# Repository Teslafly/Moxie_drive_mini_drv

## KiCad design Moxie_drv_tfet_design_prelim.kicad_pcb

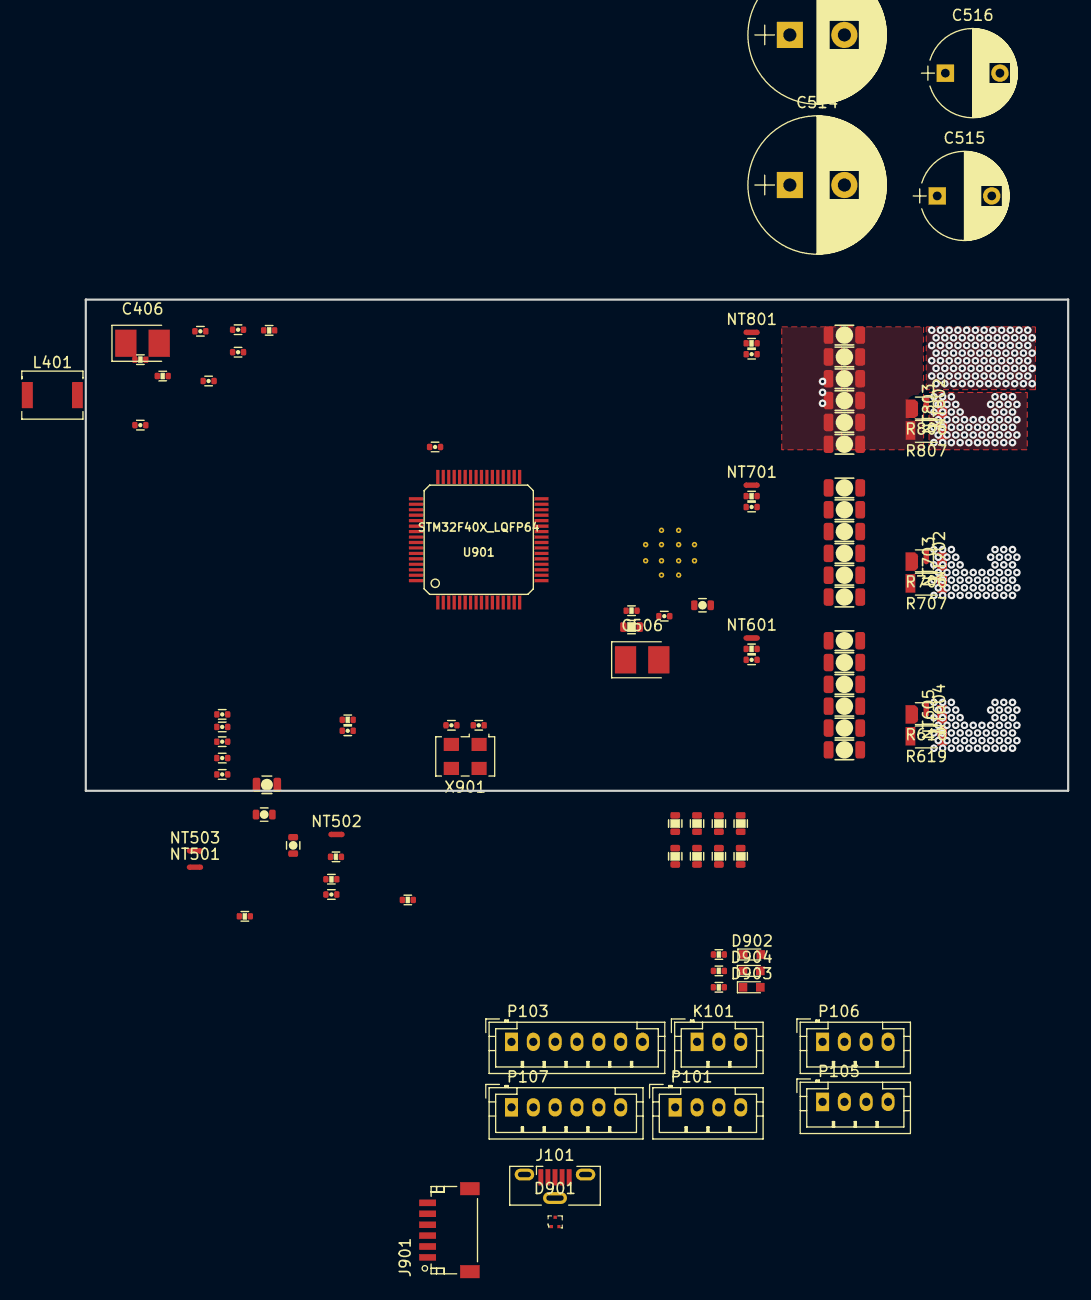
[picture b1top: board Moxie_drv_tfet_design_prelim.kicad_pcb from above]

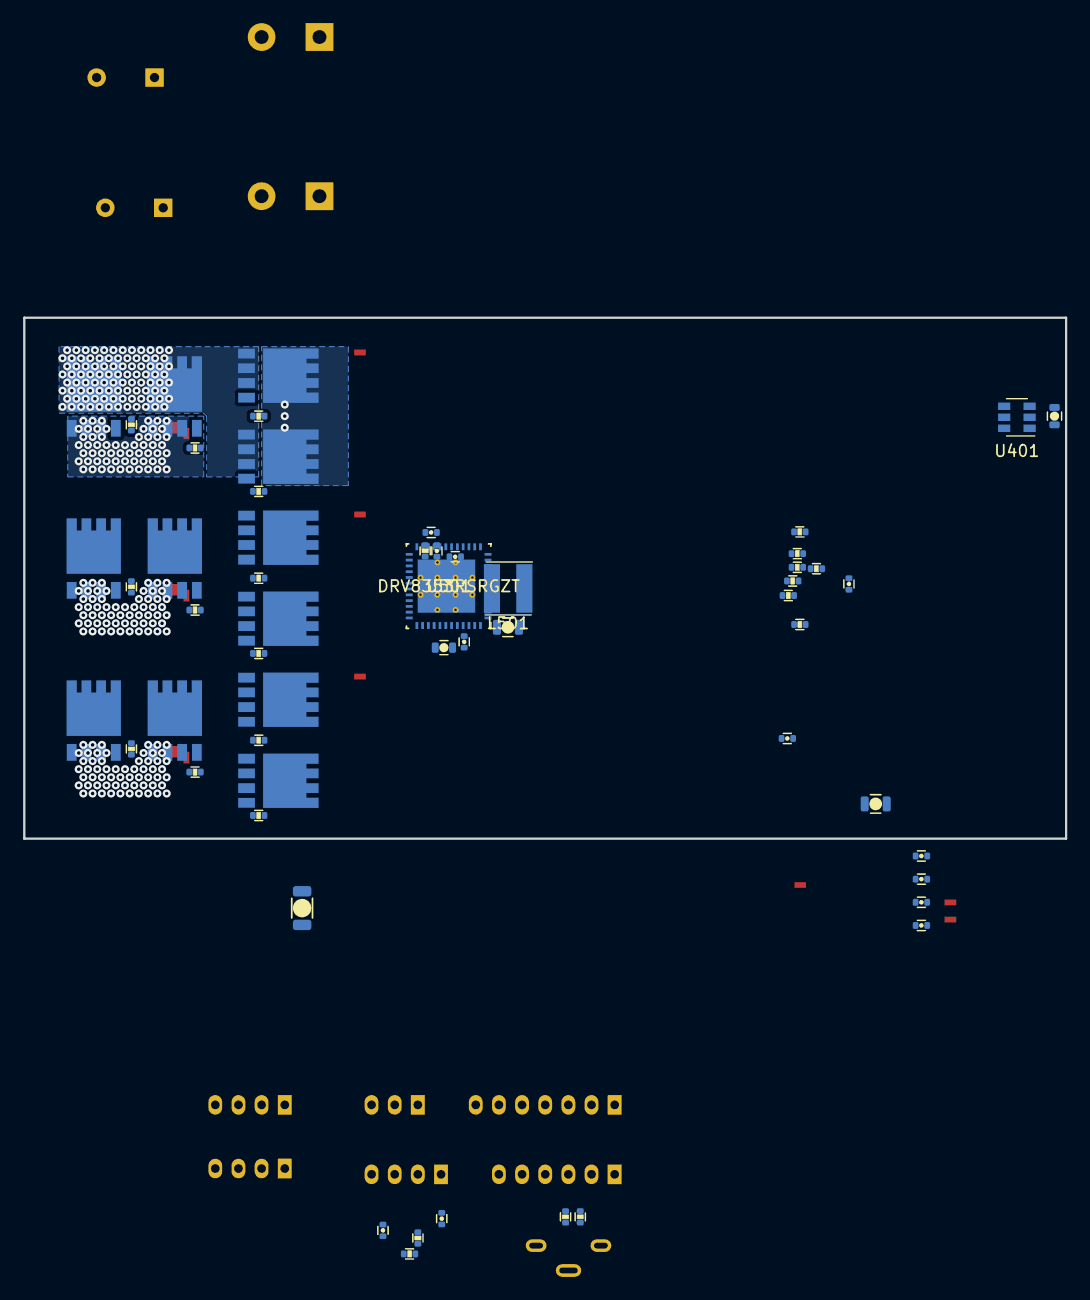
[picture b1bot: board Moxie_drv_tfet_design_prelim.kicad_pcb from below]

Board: 4 copper layers, 90.0 x 45.0 mm, 160 parts (56 on the bottom side), 109 nets, no tracks yet.

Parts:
C101, C107, C904: 100n; C_0402
C201: 4.7nf; C_0402
C202, C901, C902, C903, C905, C907, C909, C910, C911, C912: 2.2u; C_0402
C401: 2.2uf; C_0603
C402, C403, C404, C408: 100nf; C_0402
C405: 2.2uf; C_0402
C406: 100uf; CP_Tantalum_Case-B_EIA-3528-21_Reflow
C407: NP; C_0402
C501: 10uF; C_0805
C502: 1.5uF; C_1206
C503: 0.1uF; C_0603
C504: 0.1uF; C_0805
C505: 0.47uF; C_0402
C506: 0.1uF; CP_Tantalum_Case-B_EIA-3528-21_Reflow
C507: 0.047uF; C_0402
C508, C509, C511: 1uF; C_0603
C510: 0.01uF; C_0402
C512: 18nF; C_0402
C513: 22uF; C_0805
C514, C519: 560uF; CP_Radial_D12.5mm_P5.00mm
C515, C516: 20uF; CP_Radial_D8.0mm_P5.00mm
C601, C701, C801: 2.2nF; C_0402
C602, C603, C604, C605, C606, C607, C702, C703, C704, C705, C706, C707, C802, C803, C804, C805, C806, C807: 1uF; C_1206
C906, C908: 15p; C_0402
D901: TPD2EUSB30DRTR; SOT-3
D902: BLUE; LED_0603
D903: GREEN; LED_0603
D904: RED; LED_0603
J101: USB_B_Micro; USB_Micro-B_Vertical_Molex-105133-0001
J901: SWD; JST_SH_SM06B-SRSS-TB_06x1.00mm_Angled
K101: SERVO; JST_PH_B3B-PH-K_03x2.00mm_Straight
L401: 3.3uH; L_Neosid_Ms42
L501: 390uH; L_Bourns_SRN-4018
NT501, NT502, NT503, NT601, NT604, NT605, NT701, NT702, NT703, NT801, NT802, NT803: Net-Tie_2; NetTie-2_SMD_Pad0.5mm
P101: CANBUS; JST_PH_B4B-PH-K_04x2.00mm_Straight
P103: CTRL_SIGNALS; JST_PH_B7B-PH-K_07x2.00mm_Straight
P105: Serial1/tim4; JST_PH_B4B-PH-K_04x2.00mm_Straight
P106: I2C; JST_PH_B4B-PH-K_04x2.00mm_Straight
P107: HALL/Encoder; JST_PH_B6B-PH-K_06x2.00mm_Straight
Q601, Q602, Q603, Q604, Q701, Q702, Q703, Q704, Q801, Q802, Q803, Q804: TPH2R608NH,L1Q; SOP8_Advance
R101: 0Ω; R_0402
R102, R603, R703, R803: 100Ω; R_0402
R103, R104: 100kΩ; R_0402
R105, R106: 22R; R_0402
R107, R108, R109: 2k2Ω; R_0402
R110, R516: 10kΩ; R_0402
R201, R202: 120R; R_0402
R401, R901, R902, R903: 1k; R_0402
R402: R33.2k 0.1%; R_0402
R403: 10k 0.1%; R_0402
R501: 1kOhm; C_0402
R502: 10kΩ; C_0402
R503: 560kΩ; R_0402
R504: 200kΩ; R_0402
R505: 5.1kΩ; R_0402
R506: 1.0kΩ; R_0402
R507: 910mΩ; R_0603
R508, R510, R512, R514: 47kΩ; R_0603
R509, R511, R513, R515: 2.2kΩ; R_0603
R517: NTC 10kΩ; R_0402
R601, R602, R604, R605, R701, R702, R704, R705, R801, R802, R804, R805: 5Ω; R_0402
R618, R619, R706, R707, R806, R807: 1mΩ; R_1206
U401: TPS561201; SOT-23-6
U501: DRV8353RSRGZT; DRV8353RHRGZR
U901: STM32F40X_LQFP64; lqfp64_pad_mod
X901: 8MHz 10ppm; Oscillator_SMD_EuroQuartz_XO53-4pin_5.0x3.2mm

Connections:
+3V3: C202.1, C404.1, C405.1, C406.1, C407.1, C902.2, C905.2, C907.2, C909.2, C910.2, C911.2, C912.2, J901.1, L401.1, NT503.2, P103.1, P105.3, P106.3, P107.1, R101.2, R107.2, R108.2, R109.2, R110.2, R402.1, R501.1, R502.1, R516.1, R901.2, U901.1, U901.13, U901.19, U901.32, U901.48, U901.64
+12V: C401.1, C402.1, C501.1, C503.1, C513.1, R401.2, R507.2, U401.3, U501.5
+BATT: C502.1, C504.1, C511.1, C514.1, C515.1, C516.1, C519.1, C602.1, C603.1, C604.1, C605.1, C606.1, C607.1, C702.1, C703.1, C704.1, C705.1, C706.1, C707.1, C802.1, C803.1, C804.1, C805.1, C806.1, C807.1, Q601.1, Q603.1, Q701.1, Q703.1, Q801.1, Q803.1, R503.1, R514.1, U501.6, U501.43
/CAN_tranciever/CANH: P101.3, R201.1
/CAN_tranciever/CANL: P101.2, R202.1
/Microcontroller/ADC_BRAKE: P103.4, R104.1, U901.27
/Microcontroller/ADC_TEMP: C408.1, R516.2, R517.1, U901.24
/Microcontroller/ADC_THROTTLE: P103.3, R103.1, U901.26
/Microcontroller/ADC_VBUS: R514.2, R515.1, U901.11
/Microcontroller/BRAKE_SW: P103.6, U901.57
/Microcontroller/FAULT: R502.2, U501.28, U901.33
/Microcontroller/H1: U501.34, U901.41
/Microcontroller/H2: U501.36, U901.42
/Microcontroller/H3: U501.38, U901.43
/Microcontroller/HALL_1: P107.3, R107.1, U901.37
/Microcontroller/HALL_2: P107.4, R108.1, U901.38
/Microcontroller/HALL_3: P107.5, R109.1, U901.39
/Microcontroller/L1: U501.35, U901.34
/Microcontroller/L2: U501.37, U901.35
/Microcontroller/L3: U501.39, U901.36
/Microcontroller/LED_GREEN: R902.2, U901.3
/Microcontroller/LED_RED: R903.2, U901.4
/Microcontroller/SCL_2: P106.1, U901.29
/Microcontroller/SDA_2: P106.2, U901.30
/Microcontroller/SERVO: C101.2, R102.1, U901.17
/Microcontroller/TEMP_MOTOR: C107.2, P107.2, R110.1, U901.25
/Microcontroller/USART1_RX: P105.1, U901.59
/Microcontroller/USART1_TX: P105.2, U901.58
/Microcontroller/USB_DM: D901.2, R106.1, U901.44
/Microcontroller/USB_DP: D901.1, R105.1, U901.45
/Microcontroller/VCAP1: C903.2, U901.31
/Microcontroller/VCAP2: C901.2, U901.47
/drv_power_stage/3.3_IREF: C506.1, NT503.1, U501.26
/drv_power_stage/A_ISENSE: U501.25, U901.8
/drv_power_stage/A_VSENSE: R508.2, R509.1, U901.14
/drv_power_stage/B_ISENSE: U501.24, U901.9
/drv_power_stage/B_VSENSE: R510.2, R511.1, U901.15
/drv_power_stage/C_ISENSE: U501.23, U901.10
/drv_power_stage/C_VSENSE: R512.2, R513.1, U901.16
/drv_power_stage/DRV_SDO: R501.2, U501.29
/drv_power_stage/ENABLE: U501.33, U901.40
/drv_power_stage/GDRV_VSENSE: C512.1, R505.2, R506.1, U501.48
/drv_power_stage/PHASE_A: NT801.2, Q801.3, Q802.1, Q803.3, Q804.1, R508.1
/drv_power_stage/PHASE_B: NT601.2, Q601.3, Q602.1, Q603.3, Q604.1, R510.1
/drv_power_stage/PHASE_C: NT701.2, Q701.3, Q702.1, Q703.3, Q704.1, R512.1
/drv_power_stage/buck_rcl: R504.2, U501.46
/drv_power_stage/power_phase_A/H_GATE: R801.2, R804.2, U501.8
/drv_power_stage/power_phase_A/H_SWITCH: NT801.1, U501.9
/drv_power_stage/power_phase_A/L_GATE: R802.2, R805.2, U501.10
/drv_power_stage/power_phase_A/NR_SENSE: C801.1, R803.1, U501.12
/drv_power_stage/power_phase_A/PH_GND_LOW: NT802.2, Q802.3, Q804.3, R806.1, R807.1
/drv_power_stage/power_phase_A/PR_SENSE: C801.2, NT802.1, U501.11
/drv_power_stage/power_phase_B/H_GATE: R601.2, R604.2, U501.17
/drv_power_stage/power_phase_B/H_SWITCH: NT601.1, U501.16
/drv_power_stage/power_phase_B/L_GATE: R602.2, R605.2, U501.15
/drv_power_stage/power_phase_B/NR_SENSE: C601.1, R603.1, U501.13
/drv_power_stage/power_phase_B/PH_GND_LOW: NT604.2, Q602.3, Q604.3, R618.1, R619.1
/drv_power_stage/power_phase_B/PR_SENSE: C601.2, NT604.1, U501.14
/drv_power_stage/power_phase_C/H_GATE: R701.2, R704.2, U501.18
/drv_power_stage/power_phase_C/H_SWITCH: NT701.1, U501.19
/drv_power_stage/power_phase_C/L_GATE: R702.2, R705.2, U501.20
/drv_power_stage/power_phase_C/NR_SENSE: C701.1, R703.1, U501.22
/drv_power_stage/power_phase_C/PH_GND_LOW: NT702.2, Q702.3, Q704.3, R706.1, R707.1
/drv_power_stage/power_phase_C/PR_SENSE: C701.2, NT702.1, U501.21
GND: C101.1, C107.1, C201.2, C202.2, C401.2, C402.2, C404.2, C405.2, C406.2, C514.2, C515.2, C516.2, C519.2, C901.1, C903.1, C904.1, C906.2, C907.1, C908.2, C909.1, C910.1, C911.1, C912.1, D901.3, D902.2, D903.2, D904.2, J101.5, J101.6, J901.3, K101.3, NT501.2, NT502.2, P101.1, P103.2, P103.7, P105.4, P106.4, P107.6, R103.2, R104.2, R403.2, U401.1, U501.41, U901.18, U901.60, U901.63, X901.3
GNDA: C408.2, C506.2, C902.1, C905.1, NT501.1, U501.27, U901.12
GNDD: C501.2, C502.2, C503.2, C504.2, C505.2, C508.1, C509.2, C513.2, C602.2, C603.2, C604.2, C605.2, C606.2, C607.2, C702.2, C703.2, C704.2, C705.2, C706.2, C707.2, C802.2, C803.2, C804.2, C805.2, C806.2, C807.2, NT502.1, NT605.2, NT703.2, NT803.2, R504.1, R506.2, R509.2, R511.2, R513.2, R515.2, R517.2, R618.2, R619.2, R706.2, R707.2, R806.2, R807.2, U501.1, U501.49
NRST: C904.2, J901.5, U901.7
unnamed: C201.1, R201.2, R202.2
unnamed: C403.1, L401.2, U401.2
unnamed: C403.2, U401.6
unnamed: C407.2, R402.2, R403.1, U401.4
unnamed: C505.1, U501.44
unnamed: C507.1, U501.4
unnamed: C507.2, U501.3
unnamed: C508.2, U501.2
unnamed: C509.1, U501.40
unnamed: C510.1, U501.45
unnamed: C510.2, L501.2, U501.42
unnamed: C511.2, U501.7
unnamed: C512.2, L501.1, R505.1, R507.1
unnamed: C906.1, U901.5, X901.1
unnamed: C908.1, U901.6, X901.2
unnamed: D902.1, R901.1
unnamed: D903.1, R902.1
unnamed: D904.1, R903.1
unnamed: J101.2, R106.2
unnamed: J101.3, R105.2
unnamed: K101.1, R102.2
unnamed: K101.2, R101.1
unnamed: NT605.1, R603.2
unnamed: NT703.1, R703.2
unnamed: NT803.1, R803.2
unnamed: Q601.2, R601.1
unnamed: Q602.2, R602.1
unnamed: Q603.2, R604.1
unnamed: Q604.2, R605.1
unnamed: Q701.2, R701.1
unnamed: Q702.2, R702.1
unnamed: Q703.2, R704.1
unnamed: Q704.2, R705.1
unnamed: Q801.2, R801.1
unnamed: Q802.2, R802.1
unnamed: Q803.2, R804.1
unnamed: Q804.2, R805.1
unnamed: R401.1, U401.5
unnamed: R503.2, U501.47
SWCLK: J901.2, U901.49
SWDIO: J901.4, U901.46

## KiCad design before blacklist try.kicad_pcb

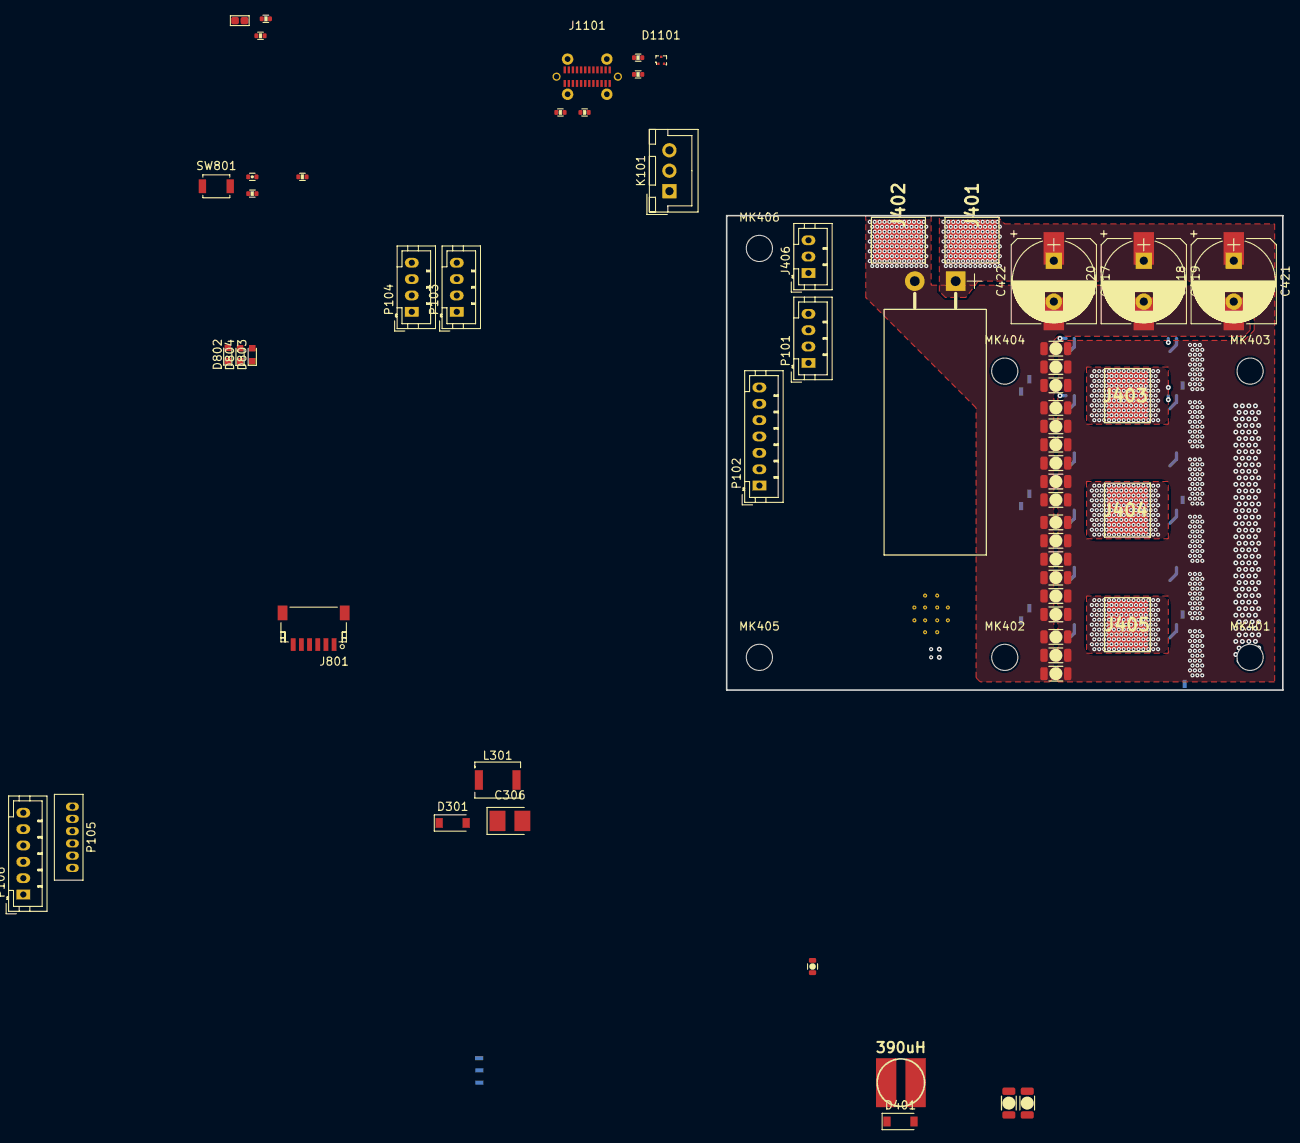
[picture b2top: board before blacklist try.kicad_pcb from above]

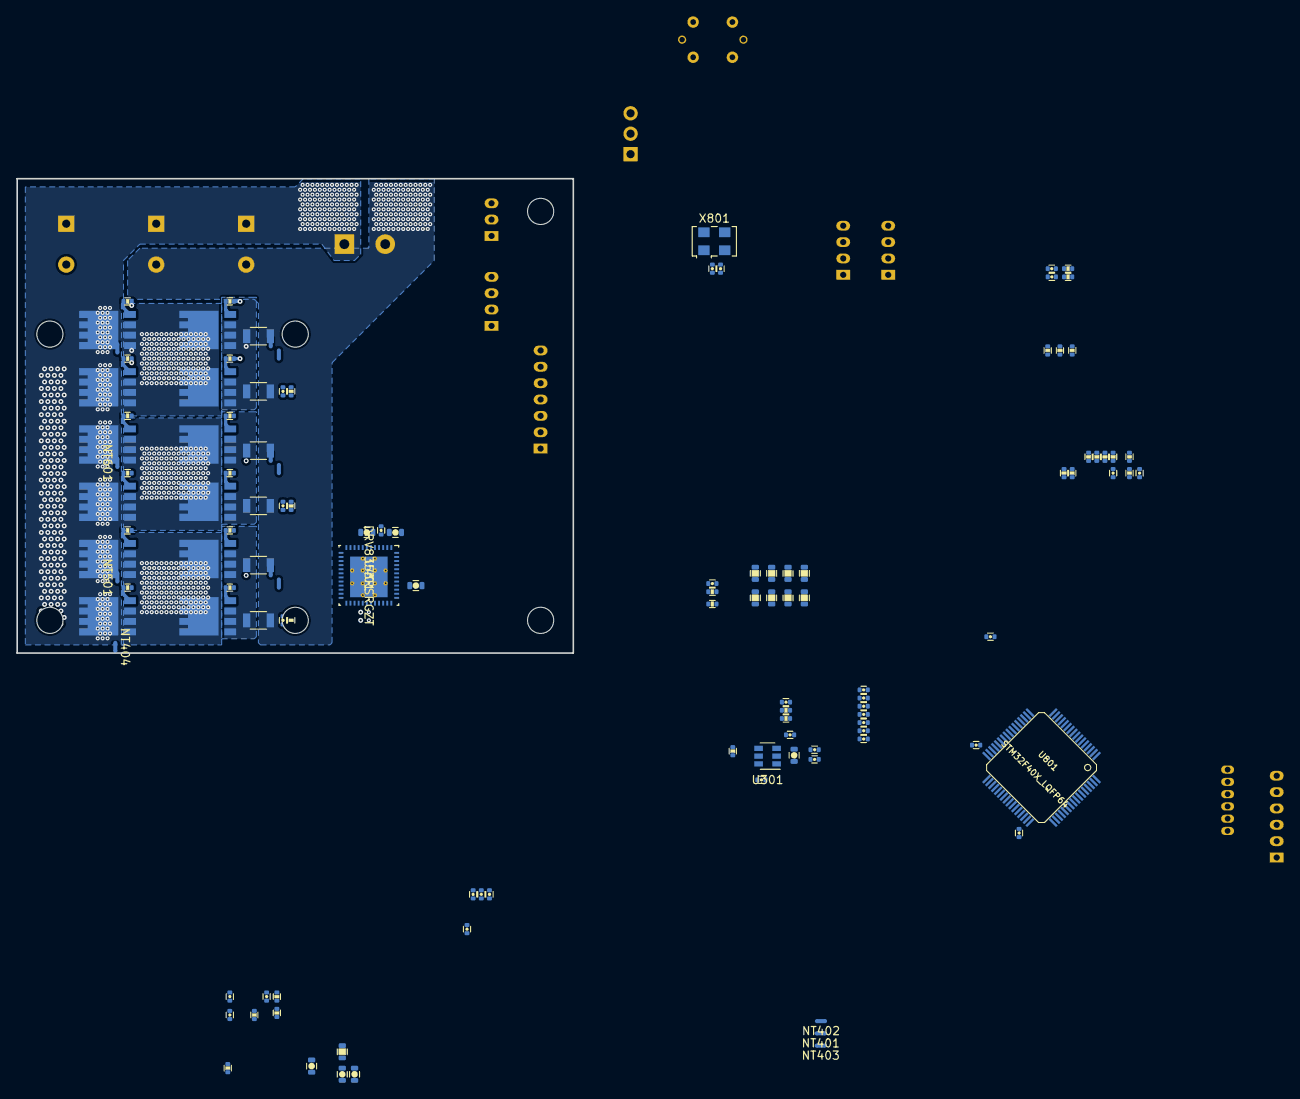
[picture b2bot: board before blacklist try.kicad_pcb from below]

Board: 4 copper layers, 68.0 x 58.0 mm, 190 parts (121 on the bottom side), 118 nets.

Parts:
C101, C102, C804, C813: 100n; C_0402
C201: 4.7nf; C_0402
C202, C801, C802, C803, C805, C807, C809, C810, C811, C812: 2.2u; C_0402
C301: 10uf; C_0603
C302, C303, C304, C423: 100nf; C_0402
C305: 2.2uf; C_0402
C306: 100uf; CP_Tantalum_Case-B_EIA-3528-21_Reflow
C307: NP; C_0402
C401, C402, C413: 10uF; C_0603
C403, C406: 0.1uF; C_0402
C404: 0.1uF; C_0603
C405: 0.47uF; C_0402
C407: 0.047uF; C_0402
C408, C409, C411: 1uF; C_0603
C410: 0.01uF; C_0402
C412: 18nF; C_0402
C414: 560uF; CP_Radial_D12.5mm_P5.00mm_horiz
C417, C419, C421: 56uF; CP_Radial_D10.0mm_P5.00mm
C418, C420, C422: 20uF; CP_Elec_10x10.5
C424, C425, C502, C503, C504, C505, C506, C507, C602, C603, C604, C605, C606, C607, C702, C703, C704, C705, C706, C707: 1uF; C_1206
C501, C601, C701: 2.2nF; C_0402
C806, C808: 15p; C_0402
D301: 1.5KExxA; D_SOD-123
D401: DFLS1100-7; D_SOD-123
D802: BLUE; LED_0603
D803: GREEN; LED_0603
D804: RED; LED_0603
D1101: TPD2EUSB30DRTR; SOT-3
J401: +Vbat; 1PAD_6x5mm
J402: Gnd; 1PAD_6x5mm
J403: A; 1PAD_6x5mm
J404: B; 1PAD_6x5mm
J405: C; 1PAD_6x5mm
J406: Conn_01x03; JST_PH_B3B-PH-K_03x2.00mm_Straight
J801: SWD; JST_SH_SM06B-SRSS-TB_06x1.00mm_Angled
J1101: USB_C_Receptacle; USB_C_receptacle_vertical
JP401: pwr_ctl_byp; J_0603
K101: SERVO; JST_XH_B03B-XH-A_03x2.50mm_Straight
L301: 3.3uH; L_Neosid_Ms42
L401: 390uH; inductor_smd_5.8mmx4.8hmm
MK401, MK402, MK403, MK404, MK405, MK406: Mounting_Hole; MountingHole_3.2mm_M3_DIN965
NT401, NT402, NT403, NT404, NT501, NT502, NT503, NT601, NT602, NT603, NT701, NT702, NT703: Net-Tie_2; NetTie-2_SMD_Pad0.5mm
P101: CANBUS; JST_PH_B4B-PH-K_04x2.00mm_Straight
P102: CTRL_SIGNALS; JST_PH_B7B-PH-K_07x2.00mm_Straight
P103: Serial1/tim4; JST_PH_B4B-PH-K_04x2.00mm_Straight
P104: I2C; JST_PH_B4B-PH-K_04x2.00mm_Straight
P105: HALL/Encoder; simple_jst-zh_1.5mm_unfinished
P106: HALL/Encoder; JST_PH_B6B-PH-K_06x2.00mm_Straight
Q501, Q502, Q503, Q504, Q601, Q602, Q603, Q604, Q701, Q702, Q703, Q704: TPH2R608NH,L1Q; SOP8_Advance
R101: 0Ω; R_0402
R102, R501, R601, R701: 100Ω; R_0402
R103, R104: 100kΩ; R_0402
R107, R108, R109: 2k2Ω; R_0402
R110, R416: 10kΩ; R_0402
R201, R202: 120R; R_0402
R301, R801, R802, R803: 1k; R_0402
R302: R33.2k 0.1%; R_0402
R303: 10k 0.1%; R_0402
R401: 1kOhm; C_0402
R402: 10kΩ; C_0402
R403: 560kΩ; R_0402
R404: 200kΩ; R_0402
R405: 5.1kΩ; R_0402
R406: 1.0kΩ; R_0402
R407: 910mΩ; R_0603
R408, R410, R412, R414: 47kΩ; R_0603
R409, R411, R413, R415: 2.2kΩ; R_0603
R417: NTC 10kΩ; R_0402
R418, R804: 10k; R_0402
R419: 22k?; R_0402
R420: 100; R_0402
R502, R503, R504, R505, R602, R603, R604, R605, R702, R703, R704, R705: 5Ω; R_0402
R506, R507, R606, R607, R706, R707: 1mΩ; R_1206
R1101, R1102: 22R; R_0402
R1103, R1104: 5.1k; R_0402
SW801: SW_Push; SW_SPST_B3U-1000P
U301: TPS561201; SOT-23-6
U401: DRV8353RSRGZT; DRV8353RHRGZR
U801: STM32F40X_LQFP64; lqfp64_pad_mod
X801: 8MHz 10ppm; Oscillator_SMD_EuroQuartz_XO53-4pin_5.0x3.2mm

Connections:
+3V3: C202.1, C304.1, C305.1, C306.1, C307.1, C802.2, C805.2, C807.2, C809.2, C810.2, C811.2, C812.2, D301.1, J801.1, L301.1, NT403.2, P102.1, P103.3, P104.3, P105.6, R101.2, R107.2, R108.2, R109.2, R110.2, R302.1, R401.1, R402.1, R416.1, R801.2, SW801.2, U801.1, U801.13, U801.19, U801.32, U801.48, U801.64
+15V: C301.1, C302.1, C401.1, C402.1, C403.1, C413.1, R301.2, R407.2, R420.2, U301.3, U401.5
+BATT: C414.1, C417.1, C418.1, C419.1, C420.1, C421.1, C422.1, C502.1, C503.1, C504.1, C505.1, C506.1, C507.1, C602.1, C603.1, C604.1, C605.1, C606.1, C607.1, C702.1, C703.1, C704.1, C705.1, C706.1, C707.1, J401.1, JP401.1, NT404.1, Q501.1, Q503.1, Q601.1, Q603.1, Q701.1, Q703.1, R414.1, R418.1
/CAN_tranciever/CANH: P101.3, R201.1
/CAN_tranciever/CANL: P101.2, R202.1
/Microcontroller/ADC_BRAKE: P102.4, R104.1, U801.27
/Microcontroller/ADC_TEMP: C423.1, R416.2, R417.1, U801.24
/Microcontroller/ADC_THROTTLE: P102.3, R103.1, U801.26
/Microcontroller/ADC_VBUS: R414.2, R415.1, U801.11
/Microcontroller/BOOT_0: C813.2, R804.1, SW801.1, U801.60
/Microcontroller/BRAKE_SW: P102.6, U801.57
/Microcontroller/FAULT: R402.2, U401.28, U801.33
/Microcontroller/H1: U401.34, U801.41
/Microcontroller/H2: U401.36, U801.42
/Microcontroller/H3: U401.38, U801.43
/Microcontroller/HALL_1: P105.4, R107.1, U801.37
/Microcontroller/HALL_2: P105.3, R108.1, U801.38
/Microcontroller/HALL_3: P105.2, R109.1, U801.39
/Microcontroller/L1: U401.35, U801.34
/Microcontroller/L2: U401.37, U801.35
/Microcontroller/L3: U401.39, U801.36
/Microcontroller/LED_GREEN: R802.2, U801.3
/Microcontroller/LED_RED: R803.2, U801.4
/Microcontroller/SCL_2: P104.1, U801.29
/Microcontroller/SDA_2: P104.2, U801.30
/Microcontroller/SERVO: C101.2, R102.1, U801.17
/Microcontroller/TEMP_MOTOR: C102.2, P105.5, R110.1, U801.25
/Microcontroller/USART1_RX: P103.1, U801.59
/Microcontroller/USART1_TX: P103.2, U801.58
/Microcontroller/VCAP1: C803.2, U801.31
/Microcontroller/VCAP2: C801.2, U801.47
/USB-C connector/D+: D1101.1, R1102.1, U801.45
/USB-C connector/D-: D1101.2, R1101.1, U801.44
/drv_power_stage/3.3_IREF: C406.1, NT403.1, U401.26
/drv_power_stage/A_ISENSE: U401.25, U801.8
/drv_power_stage/A_VSENSE: R408.2, R409.1, U801.14
/drv_power_stage/BK_BST_C: C410.1, U401.45
/drv_power_stage/BK_RT_SD: R403.2, U401.47
/drv_power_stage/BK_SW: C410.2, D401.1, L401.2, U401.42
/drv_power_stage/BK_VCC: C405.1, U401.44
/drv_power_stage/BK_VIN: C404.1, C424.1, C425.1, JP401.2, R403.1, U401.43
/drv_power_stage/BK_VOUT_RIPP: C412.2, L401.1, R405.1, R407.1
/drv_power_stage/B_ISENSE: U401.24, U801.9
/drv_power_stage/B_VSENSE: R410.2, R411.1, U801.15
/drv_power_stage/C_ISENSE: U401.23, U801.10
/drv_power_stage/C_VSENSE: R412.2, R413.1, U801.16
/drv_power_stage/DRV_SDO: R401.2, U401.29
/drv_power_stage/ENABLE: U401.33, U801.40
/drv_power_stage/GDRV_VSENSE: C412.1, R405.2, R406.1, U401.48
/drv_power_stage/PHASE_A: J403.1, NT701.2, Q701.3, Q702.1, Q703.3, Q704.1, R408.1
/drv_power_stage/PHASE_B: J404.1, NT601.2, Q601.3, Q602.1, Q603.3, Q604.1, R410.1
/drv_power_stage/PHASE_C: J405.1, NT501.2, Q501.3, Q502.1, Q503.3, Q504.1, R412.1
/drv_power_stage/buck_rcl: R404.2, U401.46
/drv_power_stage/dvdd: C409.1, U401.40
/drv_power_stage/power_phase_A/H_GATE: R702.2, R704.2, U401.8
/drv_power_stage/power_phase_A/H_SWITCH: NT701.1, U401.9
/drv_power_stage/power_phase_A/L_GATE: R703.2, R705.2, U401.10
/drv_power_stage/power_phase_A/NR_SENSE: C701.1, R701.1, U401.12
/drv_power_stage/power_phase_A/PH_GND_LOW: NT702.2, Q702.3, Q704.3, R706.1, R707.1
/drv_power_stage/power_phase_A/PR_SENSE: C701.2, NT702.1, U401.11
/drv_power_stage/power_phase_B/H_GATE: R602.2, R604.2, U401.17
/drv_power_stage/power_phase_B/H_SWITCH: NT601.1, U401.16
/drv_power_stage/power_phase_B/L_GATE: R603.2, R605.2, U401.15
/drv_power_stage/power_phase_B/NR_SENSE: C601.1, R601.1, U401.13
/drv_power_stage/power_phase_B/PH_GND_LOW: NT602.2, Q602.3, Q604.3, R606.1, R607.1
/drv_power_stage/power_phase_B/PR_SENSE: C601.2, NT602.1, U401.14
/drv_power_stage/power_phase_C/H_GATE: R502.2, R504.2, U401.18
/drv_power_stage/power_phase_C/H_SWITCH: NT501.1, U401.19
/drv_power_stage/power_phase_C/L_GATE: R503.2, R505.2, U401.20
/drv_power_stage/power_phase_C/NR_SENSE: C501.1, R501.1, U401.22
/drv_power_stage/power_phase_C/PH_GND_LOW: NT502.2, Q502.3, Q504.3, R506.1, R507.1
/drv_power_stage/power_phase_C/PR_SENSE: C501.2, NT502.1, U401.21
/drv_power_stage/pwr_ctl: J406.3, R419.2
/drv_power_stage/pwr_ctl_g: R418.2, R419.1
/drv_power_stage/sw_led: J406.1, R420.1
/drv_power_stage/vcp: C411.2, U401.7
/drv_power_stage/vdrain: C411.1, NT404.2, U401.6
/drv_power_stage/vgls: C408.2, U401.2
GND: C101.1, C102.1, C201.2, C202.2, C301.2, C302.2, C304.2, C305.2, C306.2, C801.1, C803.1, C804.1, C806.2, C807.1, C808.2, C809.1, C810.1, C811.1, C812.1, C813.1, D301.2, D802.2, D803.2, D804.2, D1101.3, J801.3, J1101.A1, J1101.A12, J1101.B1, J1101.B12, K101.3, NT401.2, NT402.2, P101.1, P102.2, P102.7, P103.4, P104.4, P105.1, R103.2, R104.2, R303.2, R804.2, R1103.2, R1104.2, U301.1, U401.41, U801.18, U801.63, X801.3
GNDA: C406.2, C423.2, C802.1, C805.1, NT401.1, U401.27, U801.12
GNDD: C401.2, C402.2, C403.2, C404.2, C405.2, C408.1, C409.2, C413.2, C414.2, C417.2, C418.2, C419.2, C420.2, C421.2, C422.2, C424.2, C425.2, C502.2, C503.2, C504.2, C505.2, C506.2, C507.2, C602.2, C603.2, C604.2, C605.2, C606.2, C607.2, C702.2, C703.2, C704.2, C705.2, C706.2, C707.2, D401.2, J402.1, J406.2, NT402.1, NT503.2, NT603.2, NT703.2, R404.1, R406.2, R409.2, R411.2, R413.2, R415.2, R417.2, R506.2, R507.2, R606.2, R607.2, R706.2, R707.2, U401.1, U401.49
NRST: C804.2, J801.5, U801.7
unnamed: C201.1, R201.2, R202.2
unnamed: C303.1, L301.2, U301.2
unnamed: C303.2, U301.6
unnamed: C307.2, R302.2, R303.1, U301.4
unnamed: C407.1, U401.4
unnamed: C407.2, U401.3
unnamed: C806.1, U801.5, X801.1
unnamed: C808.1, U801.6, X801.2
unnamed: D802.1, R801.1
unnamed: D803.1, R802.1
unnamed: D804.1, R803.1
unnamed: J1101.A4, J1101.A9, J1101.B4, J1101.B9
unnamed: J1101.A5, R1104.1
unnamed: J1101.A6, J1101.B6, R1102.2
unnamed: J1101.A7, J1101.B7, R1101.2
unnamed: J1101.B5, R1103.1
unnamed: K101.1, R102.2
unnamed: K101.2, R101.1
unnamed: NT503.1, R501.2
unnamed: NT603.1, R601.2
unnamed: NT703.1, R701.2
unnamed: Q501.2, R502.1
unnamed: Q502.2, R503.1
unnamed: Q503.2, R504.1
unnamed: Q504.2, R505.1
unnamed: Q601.2, R602.1
unnamed: Q602.2, R603.1
unnamed: Q603.2, R604.1
unnamed: Q604.2, R605.1
unnamed: Q701.2, R702.1
unnamed: Q702.2, R703.1
unnamed: Q703.2, R704.1
unnamed: Q704.2, R705.1
unnamed: R301.1, U301.5
SWCLK: J801.2, U801.49
SWDIO: J801.4, U801.46

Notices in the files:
parts and their libraries:
Copyright 2016 Accelerated Designs. All rights reserved.
